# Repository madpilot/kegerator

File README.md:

# Replacement Control Board for the Keg Master Series 3 (Model: BC168)

I acquired a Keg Master Series 3 kegerator a while ago. While it's a nice fridge, it was not without it's issues.

1. If power was cut, it would revert back to a default temperature (0.4°C degrees if I remember correctly), and displaying fahrenheit (why!). Beyond the obvious issue of it forgetting the set temperature, this was more an issue because:
2. It was running cold. Any lower than 0.4°C and the kegerator is dangerously close to below freezing. I've managed to freeze a keg and numerous bottles.

So, the obvious thing to do was to make a new controller!

This controller has a ESP32, as well as a 128x32 i²c LCD. 

I've replaced the thermistor with a Dallas ds18b20 temperature sensor (in parasitic mode so I can reuse the two-wires), and added a line for a heater relay so the board can be reused for a fermenter.

The front buttons are wired up as well. The esphome firmware I use switches out the "unit" button with a on/off button.

## Example esphome configuration

```yaml
esphome:
  name: kegerator
  
esp32:
  board: esp32-s2-saola-1

i2c:
  sda: GPIO16
  scl: GPIO15

font:
  - file: "gfonts://Roboto"
    id: font_large
    size: 18
  - file: "gfonts://Roboto"
    id: font_small
    size: 8

display:
  - platform: ssd1306_i2c
    model: "SSD1306 128x32"
    lambda: |-
      float current_temperature = id(kegerator_pid).current_temperature;
      float target_temperature = id(kegerator_pid).target_temperature;
      
      if(id(kegerator_pid).mode == CLIMATE_MODE_COOL) {
        if(!std::isnan(current_temperature)) {
          it.printf(64, 0, id(font_large), TextAlign::TOP_CENTER, "%.1f°C", current_temperature);
        } else {
          it.printf(64, 0, id(font_large), TextAlign::TOP_CENTER, "--°C");
        }
      } else {
          it.printf(64, 0, id(font_large), TextAlign::TOP_CENTER, "Off");
      } 

      if(!std::isnan(target_temperature)) {
        it.printf(64, 32, id(font_small), TextAlign::BOTTOM_CENTER, "%.1f°C", target_temperature);
      } else {
        it.printf(64, 32, id(font_small), TextAlign::BOTTOM_CENTER, "--°C");
      }
      
one_wire:
  - platform: gpio
    pin: GPIO14

sensor:
  - platform: dallas_temp
    id: temperature
    name: "Temperature"
    update_interval: 1s
    unit_of_measurement: "°C"
    device_class: "temperature"
    state_class: "measurement"
    accuracy_decimals: 1
    filters:
      - exponential_moving_average:
          alpha: 0.8
          send_every: 30

binary_sensor:
  - platform: gpio
    id: btn_temp_up
    pin:
      number: GPIO21
      inverted: true
      mode:
          input: true
          pullup: true
    filters:
       autorepeat:
        - delay: 1s
          time_off: 100ms
          time_on: 100ms

    on_click:
      lambda: |-
        float target_temperature = id(kegerator_pid).target_temperature;
        auto call = id(kegerator_pid).make_call();
        call.set_target_temperature(target_temperature + 0.1);
        call.perform();
 
  - platform: gpio
    id: btn_temp_down
    pin: 
      number: GPIO20
      inverted: true
      mode:
          input: true
          pullup: true
    filters:
       autorepeat:
        - delay: 1s
          time_off: 100ms
          time_on: 100ms
    on_click:
      lambda: |-
        float target_temperature = id(kegerator_pid).target_temperature;
        auto call = id(kegerator_pid).make_call();
        call.set_target_temperature(target_temperature - 0.1);
        call.perform();

  - platform: gpio
    id: btn_units
    pin: 
      number: GPIO19     
      inverted: true
      mode:
          input: true
          pullup: true
    on_click:
      then:
        lambda: |-
          auto call = id(kegerator_pid).make_call();
          if(id(kegerator_pid).mode == CLIMATE_MODE_COOL) {
            call.set_mode("OFF");
          } else {
            call.set_mode("COOL");
          }
          call.perform();

button:
  - platform: template
    name: "Kegerator PID Climate Autotune"
    on_press:
      - climate.pid.autotune: kegerator_pid

output:
  id: compressor
  platform: slow_pwm
  pin: GPIO18
  period: 1200s

climate:
  - platform: pid
    id: kegerator_pid
    name: "Kegerator"
    sensor: temperature
    default_target_temperature: 7°C
    cool_output: compressor
    visual:
      min_temperature: -7
      max_temperature: 32
      temperature_step: 0.1
    control_parameters:
      kp: 0.19714
      ki: 0.00028
      kd: 34.89431

logger:

api:
  password: ""

ota:
  - platform: esphome
    password: ""

wifi:
  ssid: WIFI_SSID
  password: WIFI_PASSWORD

  ap:
    ssid: "Kegerator"
    password: ""

captive_portal:
```

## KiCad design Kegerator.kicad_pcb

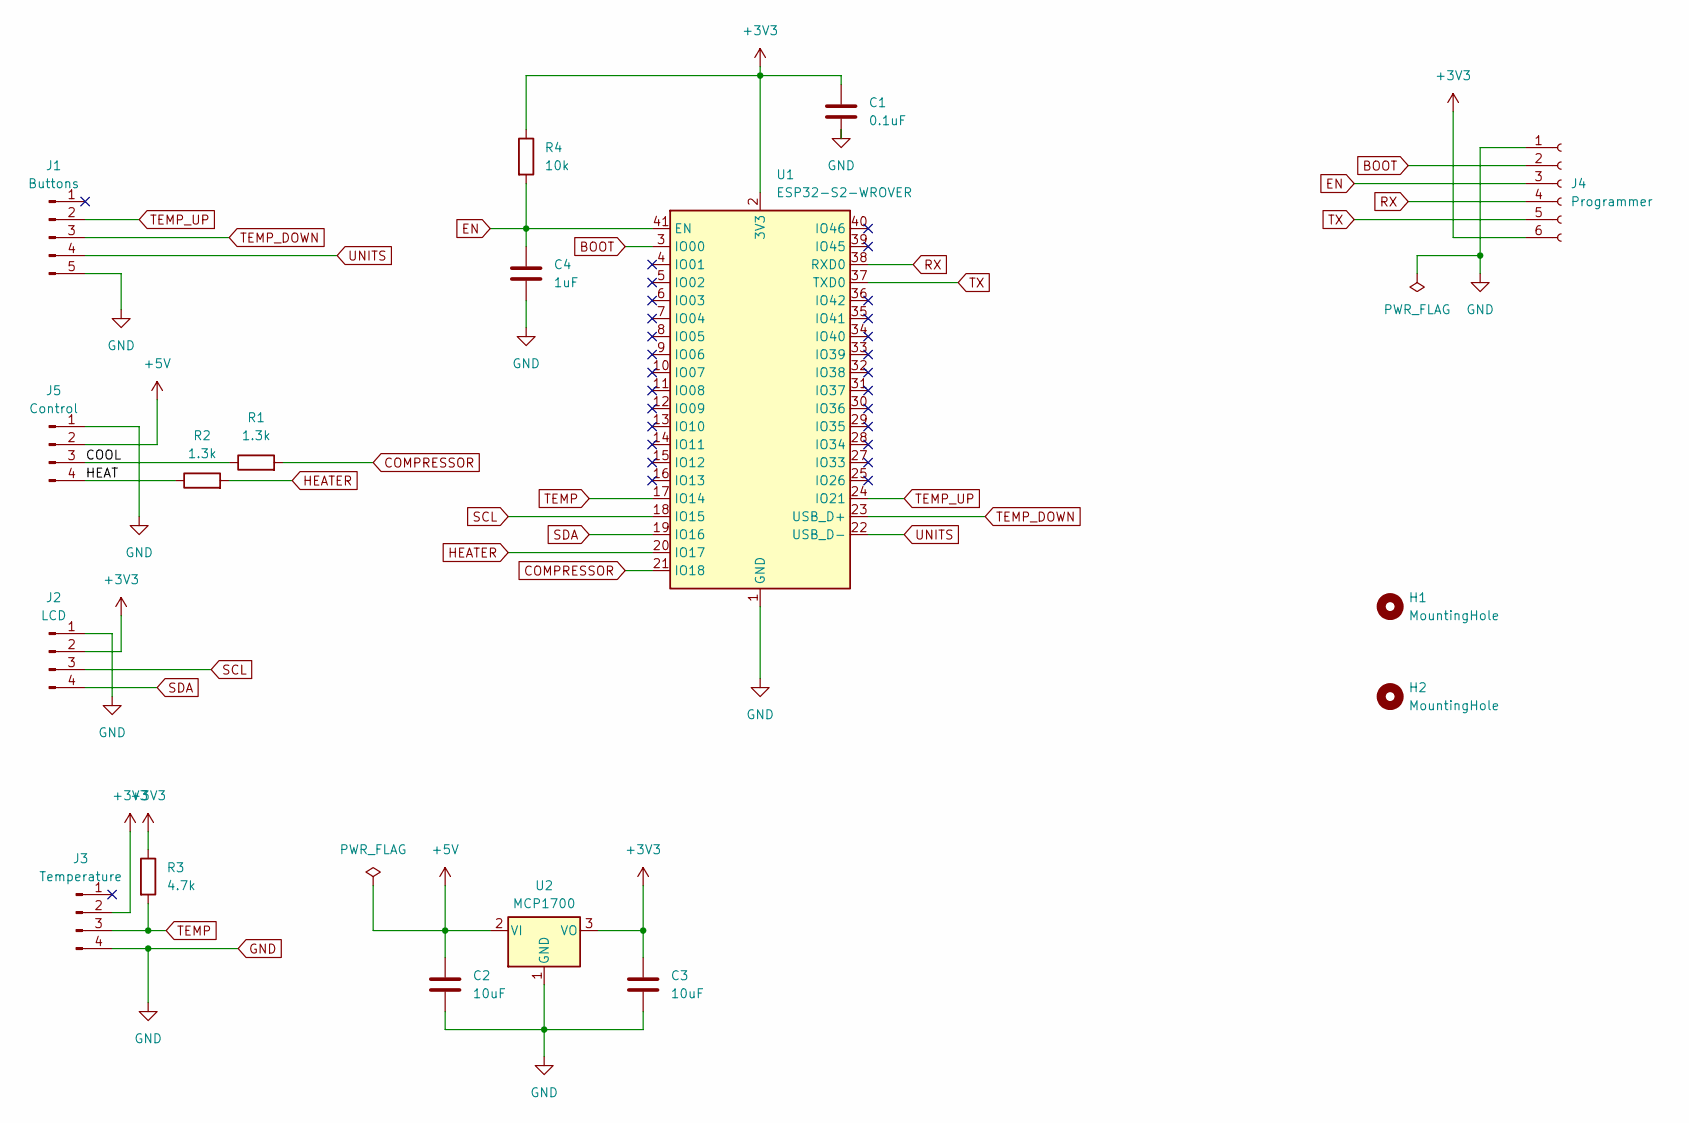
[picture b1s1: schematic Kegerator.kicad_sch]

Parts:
C1: 0.1uF; C_0805_2012Metric
C2, C3: 10uF; C_0805_2012Metric
C4: 1uF; C_0805_2012Metric
H1, H2: MountingHole; MountingHole_3mm
J1: Buttons; PinHeader_1x05_P2.54mm_Vertical
J2: LCD; 0.91 Inch OLED Module 128X32
J3: Temperature; JST_PH_B4B-PH-K_1x04_P2.00mm_Vertical
J4: Programmer; PinHeader_1x06_P2.54mm_Vertical
J5: Control; JST_XH_B4B-XH-A_1x04_P2.50mm_Vertical
R1, R2: 1.3k; R_0805_2012Metric
R3: 4.7k; R_0805_2012Metric
R4: 10k; R_0805_2012Metric
U1: ESP32-S2-WROVER
U2: MCP1700; SOT-89-3

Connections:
+3V3: C1.1, C3.1, J2.2, J3.2, J4.6, R3.1, R4.1, U1.2 (3V3), U2.3 (VO)
+5V: C2.1, J5.2, U2.2 (VI)
/COOL: J5.3, R1.1
/HEAT: J5.4, R2.1
BOOT: J4.2, U1.3 (IO00)
COMPRESSOR: R1.2, U1.21 (IO18)
EN: C4.1, J4.3, R4.2, U1.41 (EN)
GND: C1.2, C2.2, C3.2, C4.2, J1.5, J2.1, J3.4, J4.1, J5.1, U1.1 (GND), U1.26 (GND), U1.42 (GND), U1.43 (GND), U2.1 (GND)
HEATER: R2.2, U1.20 (IO17)
RX: J4.4, U1.38 (RXD0)
SCL: J2.3, U1.18 (IO15)
SDA: J2.4, U1.19 (IO16)
TEMP: J3.3, R3.2, U1.17 (IO14)
TEMP_DOWN: J1.3, U1.23 (USB_D+)
TEMP_UP: J1.2, U1.24 (IO21)
TX: J4.5, U1.37 (TXD0)
UNITS: J1.4, U1.22 (USB_D-)

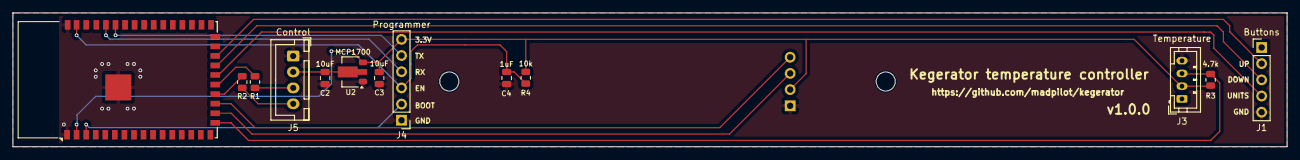
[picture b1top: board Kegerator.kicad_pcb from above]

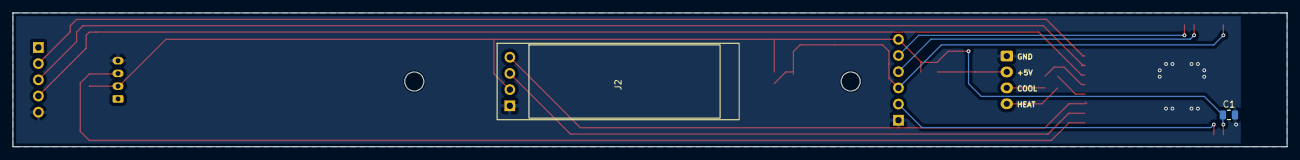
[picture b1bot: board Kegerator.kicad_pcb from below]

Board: 2 copper layers, 200.0 x 21.0 mm, 17 parts (2 on the bottom side), 17 nets.

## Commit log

2025-01-20 Allowing the temperature sensor to be able to be both really powered or parasitic power
2025-01-20 Few cleanups
2025-01-23 Adjusting LCD and screw positions
2025-01-23 Final adjustments to screw layouts and cleaning up some tracks
2025-01-27 Adding gerber directory
2025-01-27 Adding a README
2025-01-27 Fix some typos
2025-01-27 Add notes about the units button
2025-02-14 STop using GPIO26
2025-02-14 Updaing README with the correct sample code
